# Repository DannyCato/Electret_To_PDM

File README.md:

# Electret To PDM

This is a KiCad project that uses a FAN3852 to convert analog electret microphone data to PDM data. It is mounted on a 2-layer PCB with all the parts on the top layer

Additionally, it has grounded mounting pads and a power good LED to see if the connection is working.

## Usage

To be used where there is no better option to turn analog microphone signals into a digital signal. In my case, a Sigma-Delta ADC was used to convert the PDM data into PCM data so that it could more easily be converted into a WAV File for our data collection.

A 1-4 MHz Clock signal should be provided for the FAN Chip to produce PDM data. 

## Connectors
MOLEX SL 70555 series connectors (4 pin for PDM side and 2 pin for Electret side) are used for this board, but switching them out for something else is not difficult

## Schematic

## Layout

The back layer is almost entire a Ground Plane aside for the few times where wires need to cross over others.

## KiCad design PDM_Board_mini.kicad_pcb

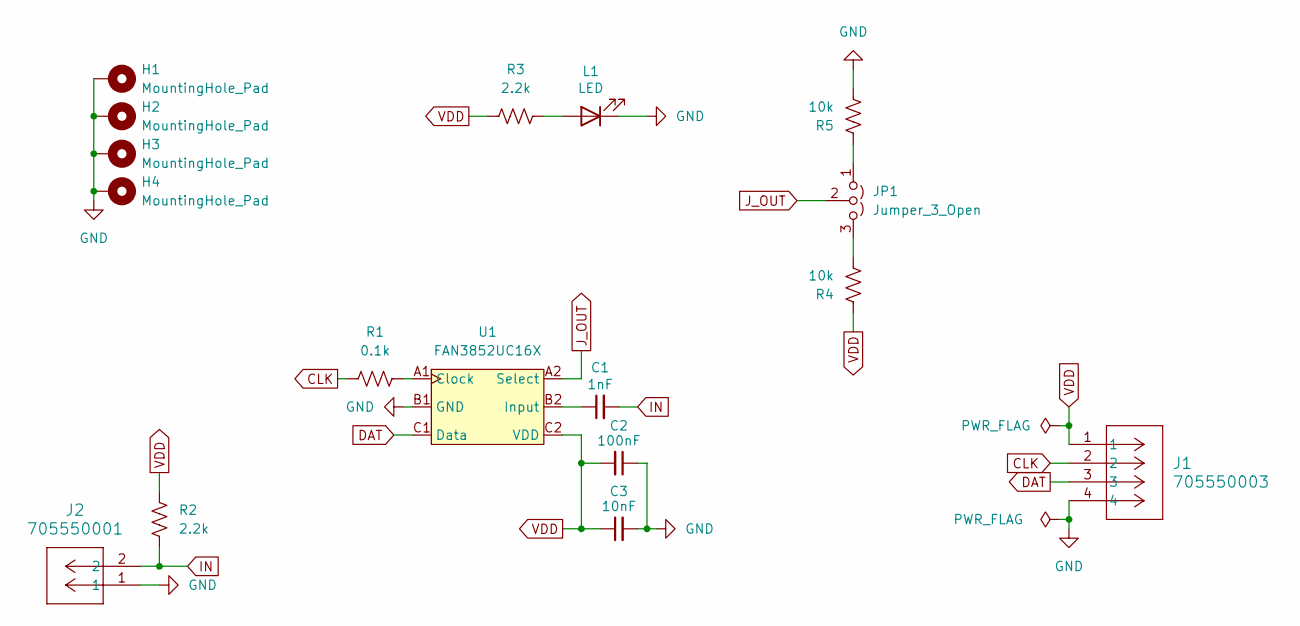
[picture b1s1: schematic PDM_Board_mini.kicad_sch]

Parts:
C1: 1nF; C_0402_1005Metric_Pad0.74x0.62mm_HandSolder
C2: 100nF; C_0603_1608Metric_Pad1.08x0.95mm_HandSolder
C3: 10nF; C_0603_1608Metric_Pad1.08x0.95mm_HandSolder
H1, H2, H3, H4: MountingHole_Pad; MountingHole_2.2mm_M2_Pad
J1: 705550003; MOLEX_SL_7055503_4PRA
J2: 705550001; MOLEX_SL_7055501_2PRA
JP1: Jumper_3_Open; PinHeader_1x03_P2.54mm_Vertical
L1: LED; LED_0603_1608Metric_Pad1.05x0.95mm_HandSolder
R1: 0.1k; R_0402_1005Metric_Pad0.72x0.64mm_HandSolder
R2, R3: 2.2k; R_0603_1608Metric_Pad0.98x0.95mm_HandSolder
R4, R5: 10k; R_0603_1608Metric_Pad0.98x0.95mm_HandSolder
U1: FAN3852UC16X; BGA6C40P2X3_84X124X50

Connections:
CLK: J1.2, R1.1
DAT: J1.3, U1.C1 (Data)
GND: C2.1, C3.2, H1.1 (1_1), H2.1 (1_1), H3.1 (1_1), H4.1 (1_1), J1.4, J2.1, L1.1 (K), R5.1, U1.B1 (GND)
IN: C1.2, J2.2, R2.2
J_OUT: JP1.2 (C), U1.A2 (Select)
unnamed: JP1.1 (A), R5.2
unnamed: JP1.3 (B), R4.1
unnamed: L1.2 (A), R3.1
unnamed: R1.2, U1.A1 (Clock)
unnamed: C1.1, U1.B2 (Input)
VDD: C2.2, C3.1, J1.1, R2.1, R3.2, R4.2, U1.C2 (VDD)

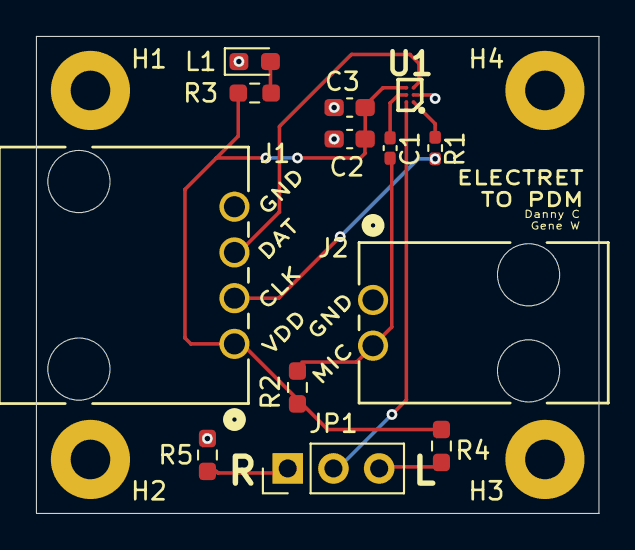
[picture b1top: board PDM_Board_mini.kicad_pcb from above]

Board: 2 copper layers, 31.2 x 26.5 mm, 17 parts (0 on the bottom side), 11 nets.

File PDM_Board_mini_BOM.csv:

"Reference","Qty","Value","DNP","Exclude from BOM","Exclude from Board","Footprint","Datasheet"
"C1","1","1nF","","","","Capacitor_SMD:C_0402_1005Metric_Pad0.74x0.62mm_HandSolder",""
"C2","1","100nF","","","","Capacitor_SMD:C_0603_1608Metric_Pad1.08x0.95mm_HandSolder",""
"C3","1","10nF","","","","Capacitor_SMD:C_0603_1608Metric_Pad1.08x0.95mm_HandSolder",""
"J1","1","705550003","","","","pdm_board_mini_library:MOLEX_SL_7055503_4PRA","https://www.molex.com/en-us/products/part-detail-pdf/7055500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"
"J2","1","705550001","","","","pdm_board_mini_library:MOLEX_SL_7055501_2PRA","https://www.molex.com/en-us/products/part-detail-pdf/7055500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"
"L1","1","LED","","","","LED_SMD:LED_0603_1608Metric_Pad1.05x0.95mm_HandSolder",""
"R1","1","0.1k","","","","Resistor_SMD:R_0402_1005Metric_Pad0.72x0.64mm_HandSolder",""
"R2,R3","2","2.2k","","","","Resistor_SMD:R_0603_1608Metric_Pad0.98x0.95mm_HandSolder",""
"R4,R5","2","10k","","","","Resistor_SMD:R_0603_1608Metric_Pad0.98x0.95mm_HandSolder",""
"U1","1","FAN3852UC16X","","","","pdm_board_mini_library:BGA6C40P2X3_84X124X50","https://www.onsemi.com/download/data-sheet/pdf/fan3852-d.pdf"

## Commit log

2026-05-06 Initial snapshot: 23 files changed fp-lib-table 4/0/0 Gerber/PDM_Board_mini-B_Cu.gbr 2188/0/0 Gerber/PDM_Board_mini-B_Mask.gbr 2040/0/0 Gerber/PDM_Board_mini-B_Paste.gbr 1995/0/0 Gerber/PDM_Board_min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
2026-05-06 Project complete
2026-05-06 Updating .gitignore
2026-05-06 Final PCB stuffs
2026-05-06 Add License
2026-05-06 Add images of schematic and layout
2026-05-06 Add FAN3852 datasheet and application note
2026-05-06 Updated PCB to 2 layer with components on only 1 side
2026-05-06 Intermediate change that should be pushed
2026-05-06 Added new gerber and image for 2 side pcb
2026-05-06 Position file added
2026-05-06 Remove ugly lock files
2026-05-06 Rename Gerber to Manufacturing Output
2026-05-07 Redo gerber, drill, and pos with correct offsets
